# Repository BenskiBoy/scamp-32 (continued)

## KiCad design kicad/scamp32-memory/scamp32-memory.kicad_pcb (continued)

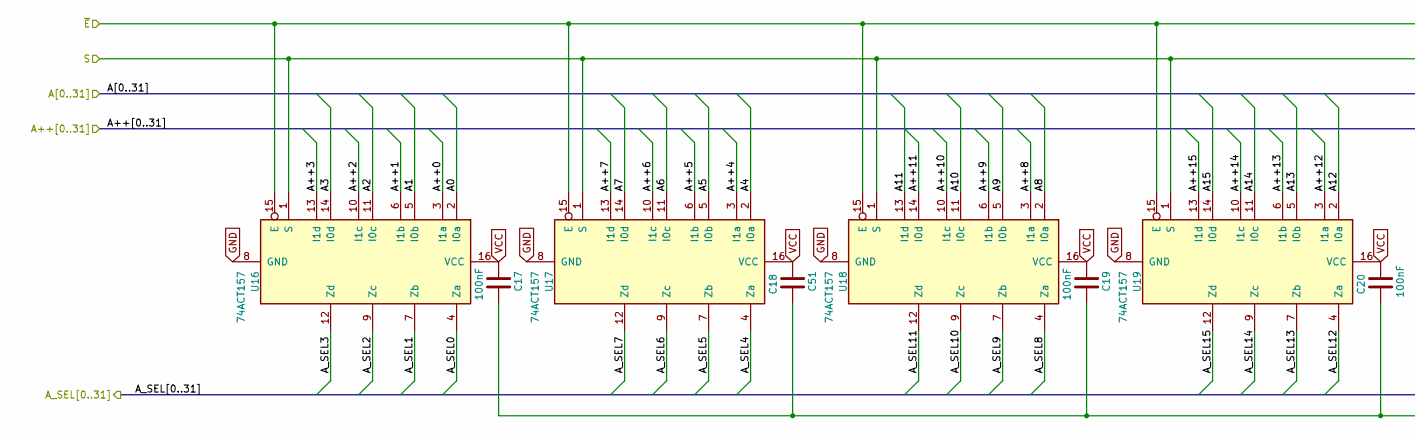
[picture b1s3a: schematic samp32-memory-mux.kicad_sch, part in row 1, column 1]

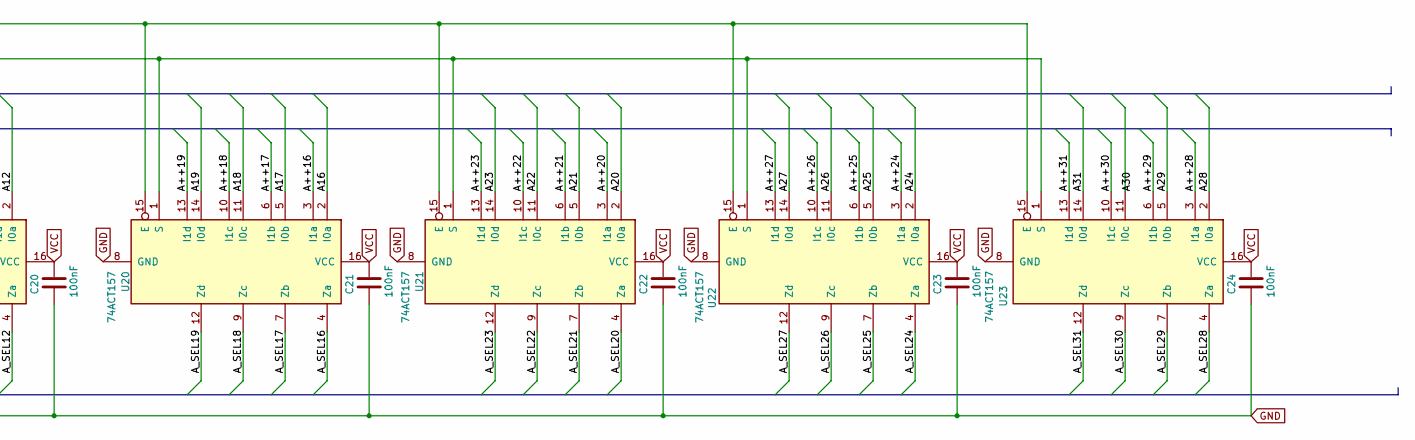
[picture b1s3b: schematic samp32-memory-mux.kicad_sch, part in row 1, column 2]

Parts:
C17, C19, C20, C21, C22, C23, C24: 100nF; C_0603_1608Metric
C18: C51; C_0603_1608Metric
U16, U17, U18, U19, U20, U21, U22, U23: 74ACT157; TSSOP-16_4.4x5mm_P0.65mm

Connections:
/A0: U16.2 (I0a); also elsewhere on the board
/A1: U16.5 (I0b); also elsewhere on the board
/A2: U16.11 (I0c); also elsewhere on the board
/A3: U16.14 (I0d); also elsewhere on the board
/A4: U17.2 (I0a); also elsewhere on the board
/A5: U17.5 (I0b); also elsewhere on the board
/A6: U17.11 (I0c); also elsewhere on the board
/A7: U17.14 (I0d); also elsewhere on the board
/A8: U18.2 (I0a); also elsewhere on the board
/A9: U18.5 (I0b); also elsewhere on the board
/A10: U18.11 (I0c); also elsewhere on the board
/A11: U18.13 (I1d); also elsewhere on the board
/A12: U19.2 (I0a); also elsewhere on the board
/A13: U19.5 (I0b); also elsewhere on the board
/A14: U19.11 (I0c); also elsewhere on the board
/A15: U19.14 (I0d); also elsewhere on the board
/A16: U20.2 (I0a); also elsewhere on the board
/A17: U20.5 (I0b); also elsewhere on the board
/A18: U20.11 (I0c); also elsewhere on the board
/A19: U20.14 (I0d); also elsewhere on the board
/A20: U21.2 (I0a); also elsewhere on the board
/A21: U21.5 (I0b); also elsewhere on the board
/A22: U21.11 (I0c); also elsewhere on the board
/A23: U21.14 (I0d); also elsewhere on the board
/A24: U22.2 (I0a); also elsewhere on the board
/A25: U22.5 (I0b); also elsewhere on the board
/A26: U22.11 (I0c); also elsewhere on the board
/A27: U22.14 (I0d); also elsewhere on the board
/A28: U23.2 (I0a); also elsewhere on the board
/A29: U23.5 (I0b); also elsewhere on the board
/A31: U23.14 (I0d); also elsewhere on the board
/samp32-memory-mux/A++0: U16.3 (I1a); also elsewhere on the board
/samp32-memory-mux/A++1: U16.6 (I1b); also elsewhere on the board
/samp32-memory-mux/A++2: U16.10 (I1c); also elsewhere on the board
/samp32-memory-mux/A++3: U16.13 (I1d); also elsewhere on the board
/samp32-memory-mux/A++4: U17.3 (I1a); also elsewhere on the board
/samp32-memory-mux/A++5: U17.6 (I1b); also elsewhere on the board
/samp32-memory-mux/A++6: U17.10 (I1c); also elsewhere on the board
/samp32-memory-mux/A++7: U17.13 (I1d); also elsewhere on the board
/samp32-memory-mux/A++8: U18.3 (I1a); also elsewhere on the board
/samp32-memory-mux/A++9: U18.6 (I1b); also elsewhere on the board
/samp32-memory-mux/A++10: U18.10 (I1c); also elsewhere on the board
/samp32-memory-mux/A++11: U18.14 (I0d); also elsewhere on the board
/samp32-memory-mux/A++12: U19.3 (I1a); also elsewhere on the board
/samp32-memory-mux/A++13: U19.6 (I1b); also elsewhere on the board
/samp32-memory-mux/A++14: U19.10 (I1c); also elsewhere on the board
/samp32-memory-mux/A++15: U19.13 (I1d); also elsewhere on the board
/samp32-memory-mux/A++16: U20.3 (I1a); also elsewhere on the board
/samp32-memory-mux/A++17: U20.6 (I1b); also elsewhere on the board
/samp32-memory-mux/A++18: U20.10 (I1c); also elsewhere on the board
/samp32-memory-mux/A++19: U20.13 (I1d); also elsewhere on the board
/samp32-memory-mux/A++20: U21.3 (I1a); also elsewhere on the board
/samp32-memory-mux/A++21: U21.6 (I1b); also elsewhere on the board
/samp32-memory-mux/A++22: U21.10 (I1c); also elsewhere on the board
/samp32-memory-mux/A++23: U21.13 (I1d); also elsewhere on the board
/samp32-memory-mux/A++24: U22.3 (I1a); also elsewhere on the board
/samp32-memory-mux/A++25: U22.6 (I1b); also elsewhere on the board
/samp32-memory-mux/A++26: U22.10 (I1c); also elsewhere on the board
/samp32-memory-mux/A++27: U22.13 (I1d); also elsewhere on the board
/samp32-memory-mux/A++28: U23.3 (I1a); also elsewhere on the board
/samp32-memory-mux/A++29: U23.6 (I1b); also elsewhere on the board
/samp32-memory-mux/A++30: U23.10 (I1c); also elsewhere on the board
/samp32-memory-mux/A++31: U23.13 (I1d); also elsewhere on the board
/samp32-memory-mux/A_SEL0: U16.4 (Za); also elsewhere on the board
/samp32-memory-mux/A_SEL1: U16.7 (Zb); also elsewhere on the board
/samp32-memory-mux/A_SEL2: U16.9 (Zc); also elsewhere on the board
/samp32-memory-mux/A_SEL3: U16.12 (Zd); also elsewhere on the board
/samp32-memory-mux/A_SEL4: U17.4 (Za); also elsewhere on the board
/samp32-memory-mux/A_SEL5: U17.7 (Zb); also elsewhere on the board
/samp32-memory-mux/A_SEL6: U17.9 (Zc); also elsewhere on the board
/samp32-memory-mux/A_SEL7: U17.12 (Zd); also elsewhere on the board
/samp32-memory-mux/A_SEL8: U18.4 (Za); also elsewhere on the board
/samp32-memory-mux/A_SEL9: U18.7 (Zb); also elsewhere on the board
/samp32-memory-mux/A_SEL10: U18.9 (Zc); also elsewhere on the board
/samp32-memory-mux/A_SEL11: U18.12 (Zd); also elsewhere on the board
/samp32-memory-mux/A_SEL12: U19.4 (Za); also elsewhere on the board
/samp32-memory-mux/A_SEL13: U19.7 (Zb); also elsewhere on the board
/samp32-memory-mux/A_SEL14: U19.9 (Zc); also elsewhere on the board
/samp32-memory-mux/A_SEL15: U19.12 (Zd); also elsewhere on the board
/samp32-memory-mux/A_SEL16: U20.4 (Za); also elsewhere on the board
/samp32-memory-mux/A_SEL17: U20.7 (Zb); also elsewhere on the board
/samp32-memory-mux/A_SEL18: U20.9 (Zc); also elsewhere on the board
/samp32-memory-mux/A_SEL19: U20.12 (Zd)
/samp32-memory-mux/A_SEL20: U21.4 (Za)
/samp32-memory-mux/A_SEL21: U21.7 (Zb)
/samp32-memory-mux/A_SEL22: U21.9 (Zc)
/samp32-memory-mux/A_SEL23: U21.12 (Zd)
/samp32-memory-mux/A_SEL24: U22.4 (Za)
/samp32-memory-mux/A_SEL25: U22.7 (Zb)
/samp32-memory-mux/A_SEL26: U22.9 (Zc)
/samp32-memory-mux/A_SEL27: U22.12 (Zd)
/samp32-memory-mux/A_SEL28: U23.4 (Za)
/samp32-memory-mux/A_SEL29: U23.7 (Zb)
/samp32-memory-mux/A_SEL30: U23.9 (Zc)
/samp32-memory-mux/A_SEL31: U23.12 (Zd)
/samp32-memory-mux/S: U16.1 (S), U17.1 (S), U18.1 (S), U19.1 (S), U20.1 (S), U21.1 (S), U22.1 (S), U23.1 (S); also elsewhere on the board
GND: C17.2, C18.1, C19.2, C20.1, C21.1, C22.1, C23.1, C24.1, U16.8 (GND), U16.15 (E), U17.8 (GND), U17.15 (E), U18.8 (GND), U18.15 (E), U19.8 (GND), U19.15 (E), U20.8 (GND), U20.15 (E), U21.8 (GND), U21.15 (E), U22.8 (GND), U22.15 (E), U23.8 (GND), U23.15 (E); also elsewhere on the board
VCC: C17.1, C18.2, C19.1, C20.2, C21.2, C22.2, C23.2, C24.2, U16.16 (VCC), U17.16 (VCC), U18.16 (VCC), U19.16 (VCC), U20.16 (VCC), U21.16 (VCC), U22.16 (VCC), U23.16 (VCC); also elsewhere on the board

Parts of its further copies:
C25, C27, C28, C29, C30, C31, C32: 100nF; C_0603_1608Metric
C26: C51; C_0603_1608Metric
U24, U25, U26, U27, U28, U29, U30, U31: 74ACT157; TSSOP-16_4.4x5mm_P0.65mm

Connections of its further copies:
/A0: U24.2 (I0a); also elsewhere on the board
/A1: U24.5 (I0b); also elsewhere on the board
/A2: U24.11 (I0c); also elsewhere on the board
/A3: U24.14 (I0d); also elsewhere on the board
/A4: U25.2 (I0a); also elsewhere on the board
/A5: U25.5 (I0b); also elsewhere on the board
/A6: U25.11 (I0c); also elsewhere on the board
/A7: U25.14 (I0d); also elsewhere on the board
/A8: U26.2 (I0a); also elsewhere on the board
/A9: U26.5 (I0b); also elsewhere on the board
/A10: U26.11 (I0c); also elsewhere on the board
/A11: U26.13 (I1d); also elsewhere on the board
/A12: U27.2 (I0a); also elsewhere on the board
/A13: U27.5 (I0b); also elsewhere on the board
/A14: U27.11 (I0c); also elsewhere on the board
/A15: U27.14 (I0d); also elsewhere on the board
/A16: U28.2 (I0a); also elsewhere on the board
/A17: U28.5 (I0b); also elsewhere on the board
/A18: U28.11 (I0c); also elsewhere on the board
/A19: U28.14 (I0d); also elsewhere on the board
/A20: U29.2 (I0a); also elsewhere on the board
/A21: U29.5 (I0b); also elsewhere on the board
/A22: U29.11 (I0c); also elsewhere on the board
/A23: U29.14 (I0d); also elsewhere on the board
/A24: U30.2 (I0a); also elsewhere on the board
/A25: U30.5 (I0b); also elsewhere on the board
/A26: U30.11 (I0c); also elsewhere on the board
/A27: U30.14 (I0d); also elsewhere on the board
/A28: U31.2 (I0a); also elsewhere on the board
/A29: U31.5 (I0b); also elsewhere on the board
/A31: U31.14 (I0d); also elsewhere on the board
/samp32-memory-mux1/A_SEL19: U28.12 (Zd)
/samp32-memory-mux1/A_SEL20: U29.4 (Za)
/samp32-memory-mux1/A_SEL21: U29.7 (Zb)
/samp32-memory-mux1/A_SEL22: U29.9 (Zc)
/samp32-memory-mux1/A_SEL23: U29.12 (Zd)
/samp32-memory-mux1/A_SEL24: U30.4 (Za)
/samp32-memory-mux1/A_SEL25: U30.7 (Zb)
/samp32-memory-mux1/A_SEL26: U30.9 (Zc)
/samp32-memory-mux1/A_SEL27: U30.12 (Zd)
/samp32-memory-mux1/A_SEL28: U31.4 (Za)
/samp32-memory-mux1/A_SEL29: U31.7 (Zb)
/samp32-memory-mux1/A_SEL30: U31.9 (Zc)
/samp32-memory-mux1/A_SEL31: U31.12 (Zd)
/samp32-memory-mux1/S: U24.1 (S), U25.1 (S), U26.1 (S), U27.1 (S), U28.1 (S), U29.1 (S), U30.1 (S), U31.1 (S); also elsewhere on the board
/samp32-memory-mux/A++0: U24.3 (I1a); also elsewhere on the board
/samp32-memory-mux/A++1: U24.6 (I1b); also elsewhere on the board
/samp32-memory-mux/A++2: U24.10 (I1c); also elsewhere on the board
/samp32-memory-mux/A++3: U24.13 (I1d); also elsewhere on the board
/samp32-memory-mux/A++4: U25.3 (I1a); also elsewhere on the board
/samp32-memory-mux/A++5: U25.6 (I1b); also elsewhere on the board
/samp32-memory-mux/A++6: U25.10 (I1c); also elsewhere on the board
/samp32-memory-mux/A++7: U25.13 (I1d); also elsewhere on the board
/samp32-memory-mux/A++8: U26.3 (I1a); also elsewhere on the board
/samp32-memory-mux/A++9: U26.6 (I1b); also elsewhere on the board
/samp32-memory-mux/A++10: U26.10 (I1c); also elsewhere on the board
/samp32-memory-mux/A++11: U26.14 (I0d); also elsewhere on the board
/samp32-memory-mux/A++12: U27.3 (I1a); also elsewhere on the board
/samp32-memory-mux/A++13: U27.6 (I1b); also elsewhere on the board
/samp32-memory-mux/A++14: U27.10 (I1c); also elsewhere on the board
/samp32-memory-mux/A++15: U27.13 (I1d); also elsewhere on the board
/samp32-memory-mux/A++16: U28.3 (I1a); also elsewhere on the board
/samp32-memory-mux/A++17: U28.6 (I1b); also elsewhere on the board
/samp32-memory-mux/A++18: U28.10 (I1c); also elsewhere on the board
/samp32-memory-mux/A++19: U28.13 (I1d); also elsewhere on the board
/samp32-memory-mux/A++20: U29.3 (I1a); also elsewhere on the board
/samp32-memory-mux/A++21: U29.6 (I1b); also elsewhere on the board
/samp32-memory-mux/A++22: U29.10 (I1c); also elsewhere on the board
/samp32-memory-mux/A++23: U29.13 (I1d); also elsewhere on the board
/samp32-memory-mux/A++24: U30.3 (I1a); also elsewhere on the board
/samp32-memory-mux/A++25: U30.6 (I1b); also elsewhere on the board
/samp32-memory-mux/A++26: U30.10 (I1c); also elsewhere on the board
/samp32-memory-mux/A++27: U30.13 (I1d); also elsewhere on the board
/samp32-memory-mux/A++28: U31.3 (I1a); also elsewhere on the board
/samp32-memory-mux/A++29: U31.6 (I1b); also elsewhere on the board
/samp32-memory-mux/A++30: U31.10 (I1c); also elsewhere on the board
/samp32-memory-mux/A++31: U31.13 (I1d); also elsewhere on the board
/samp32-memory-mux/A_SEL0: U24.4 (Za); also elsewhere on the board
/samp32-memory-mux/A_SEL1: U24.7 (Zb); also elsewhere on the board
/samp32-memory-mux/A_SEL2: U24.9 (Zc); also elsewhere on the board
/samp32-memory-mux/A_SEL3: U24.12 (Zd); also elsewhere on the board
/samp32-memory-mux/A_SEL4: U25.4 (Za); also elsewhere on the board
/samp32-memory-mux/A_SEL5: U25.7 (Zb); also elsewhere on the board
/samp32-memory-mux/A_SEL6: U25.9 (Zc); also elsewhere on the board
/samp32-memory-mux/A_SEL7: U25.12 (Zd); also elsewhere on the board
/samp32-memory-mux/A_SEL8: U26.4 (Za); also elsewhere on the board
/samp32-memory-mux/A_SEL9: U26.7 (Zb); also elsewhere on the board
/samp32-memory-mux/A_SEL10: U26.9 (Zc); also elsewhere on the board
/samp32-memory-mux/A_SEL11: U26.12 (Zd); also elsewhere on the board
/samp32-memory-mux/A_SEL12: U27.4 (Za); also elsewhere on the board
/samp32-memory-mux/A_SEL13: U27.7 (Zb); also elsewhere on the board
/samp32-memory-mux/A_SEL14: U27.9 (Zc); also elsewhere on the board
/samp32-memory-mux/A_SEL15: U27.12 (Zd); also elsewhere on the board
/samp32-memory-mux/A_SEL16: U28.4 (Za); also elsewhere on the board
/samp32-memory-mux/A_SEL17: U28.7 (Zb); also elsewhere on the board
/samp32-memory-mux/A_SEL18: U28.9 (Zc); also elsewhere on the board
GND: C25.2, C26.1, C27.2, C28.1, C29.1, C30.1, C31.1, C32.1, U24.8 (GND), U24.15 (E), U25.8 (GND), U25.15 (E), U26.8 (GND), U26.15 (E), U27.8 (GND), U27.15 (E), U28.8 (GND), U28.15 (E), U29.8 (GND), U29.15 (E), U30.8 (GND), U30.15 (E), U31.8 (GND), U31.15 (E); also elsewhere on the board
VCC: C25.1, C26.2, C27.1, C28.2, C29.2, C30.2, C31.2, C32.2, U24.16 (VCC), U25.16 (VCC), U26.16 (VCC), U27.16 (VCC), U28.16 (VCC), U29.16 (VCC), U30.16 (VCC), U31.16 (VCC); also elsewhere on the board

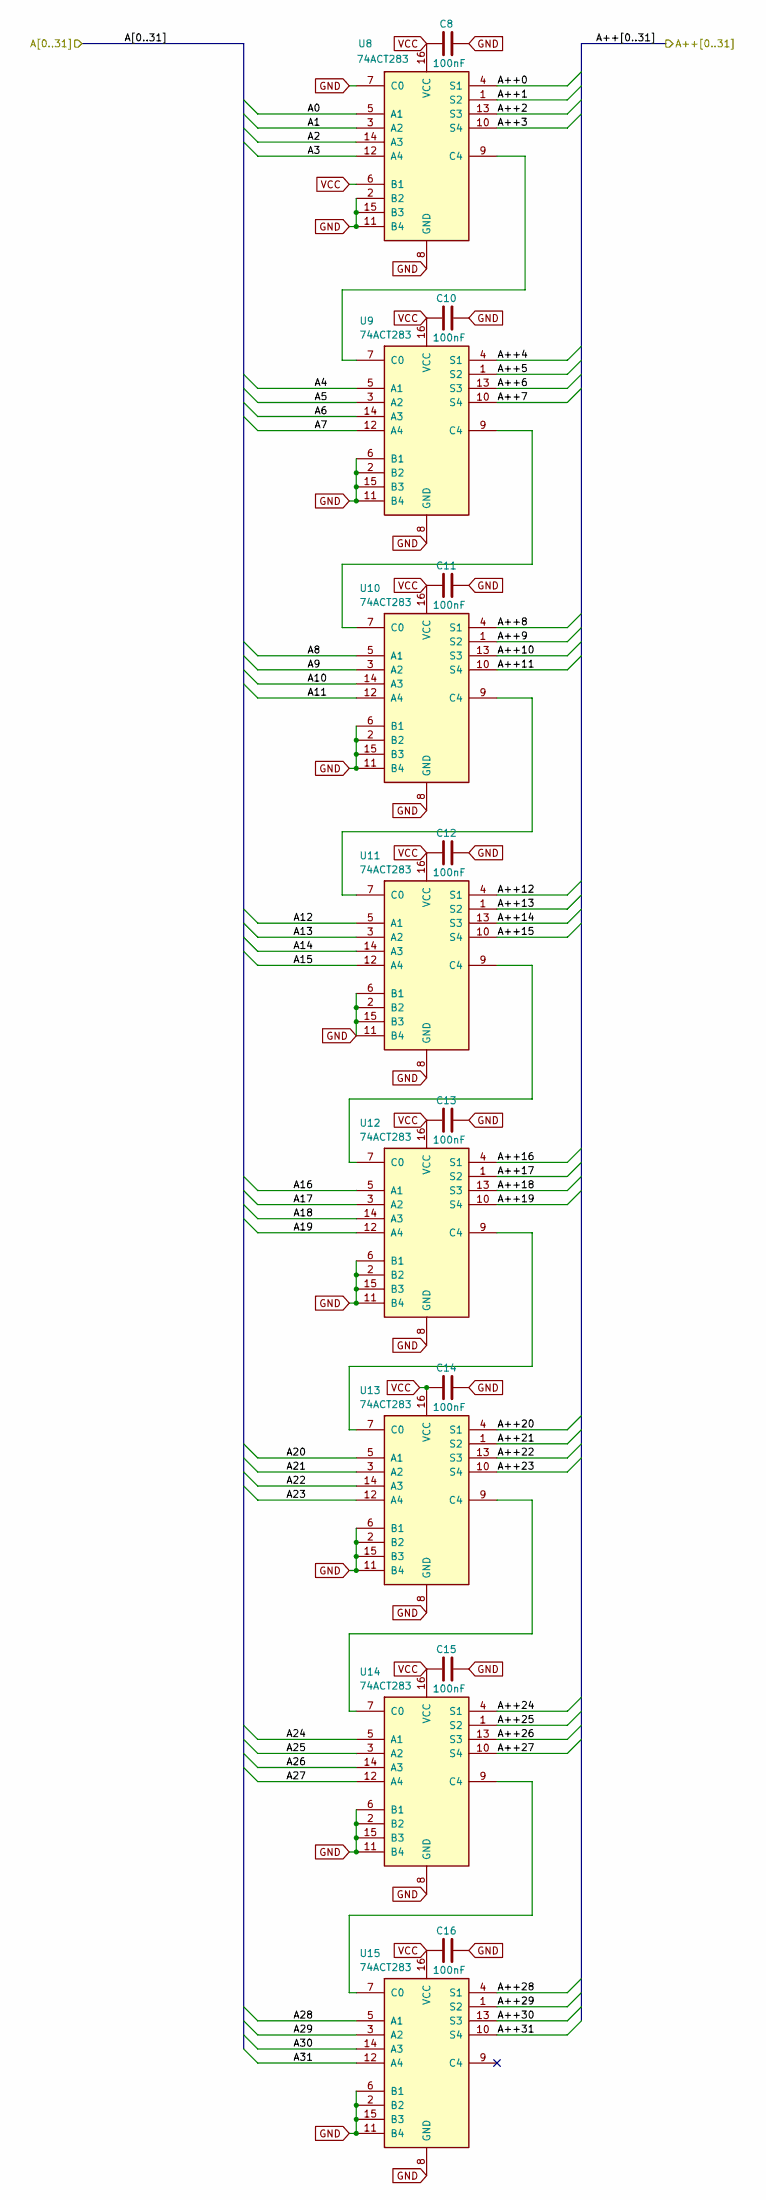
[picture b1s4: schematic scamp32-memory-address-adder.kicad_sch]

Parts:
C8, C10, C11, C12, C13, C14, C15, C16: 100nF; C_0603_1608Metric
U8, U9, U10, U11, U12, U13, U14, U15: 74ACT283; TSSOP-16_4.4x5mm_P0.65mm

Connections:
/A0: U8.5 (A1); also elsewhere on the board
/A1: U8.3 (A2); also elsewhere on the board
/A2: U8.14 (A3); also elsewhere on the board
/A3: U8.12 (A4); also elsewhere on the board
/A4: U9.5 (A1); also elsewhere on the board
/A5: U9.3 (A2); also elsewhere on the board
/A6: U9.14 (A3); also elsewhere on the board
/A7: U9.12 (A4); also elsewhere on the board
/A8: U10.5 (A1); also elsewhere on the board
/A9: U10.3 (A2); also elsewhere on the board
/A10: U10.14 (A3); also elsewhere on the board
/A11: U10.12 (A4); also elsewhere on the board
/A12: U11.5 (A1); also elsewhere on the board
/A13: U11.3 (A2); also elsewhere on the board
/A14: U11.14 (A3); also elsewhere on the board
/A15: U11.12 (A4); also elsewhere on the board
/A16: U12.5 (A1); also elsewhere on the board
/A17: U12.3 (A2); also elsewhere on the board
/A18: U12.14 (A3); also elsewhere on the board
/A19: U12.12 (A4); also elsewhere on the board
/A20: U13.5 (A1); also elsewhere on the board
/A21: U13.3 (A2); also elsewhere on the board
/A22: U13.14 (A3); also elsewhere on the board
/A23: U13.12 (A4); also elsewhere on the board
/A24: U14.5 (A1); also elsewhere on the board
/A25: U14.3 (A2); also elsewhere on the board
/A26: U14.14 (A3); also elsewhere on the board
/A27: U14.12 (A4); also elsewhere on the board
/A28: U15.5 (A1); also elsewhere on the board
/A29: U15.3 (A2); also elsewhere on the board
/A30: U15.14 (A3); also elsewhere on the board
/A31: U15.12 (A4); also elsewhere on the board
/samp32-memory-mux/A++0: U8.4 (S1); also elsewhere on the board
/samp32-memory-mux/A++1: U8.1 (S2); also elsewhere on the board
/samp32-memory-mux/A++2: U8.13 (S3); also elsewhere on the board
/samp32-memory-mux/A++3: U8.10 (S4); also elsewhere on the board
/samp32-memory-mux/A++4: U9.4 (S1); also elsewhere on the board
/samp32-memory-mux/A++5: U9.1 (S2); also elsewhere on the board
/samp32-memory-mux/A++6: U9.13 (S3); also elsewhere on the board
/samp32-memory-mux/A++7: U9.10 (S4); also elsewhere on the board
/samp32-memory-mux/A++8: U10.4 (S1); also elsewhere on the board
/samp32-memory-mux/A++9: U10.1 (S2); also elsewhere on the board
/samp32-memory-mux/A++10: U10.13 (S3); also elsewhere on the board
/samp32-memory-mux/A++11: U10.10 (S4); also elsewhere on the board
/samp32-memory-mux/A++12: U11.4 (S1); also elsewhere on the board
/samp32-memory-mux/A++13: U11.1 (S2); also elsewhere on the board
/samp32-memory-mux/A++14: U11.13 (S3); also elsewhere on the board
/samp32-memory-mux/A++15: U11.10 (S4); also elsewhere on the board
/samp32-memory-mux/A++16: U12.4 (S1); also elsewhere on the board
/samp32-memory-mux/A++17: U12.1 (S2); also elsewhere on the board
/samp32-memory-mux/A++18: U12.13 (S3); also elsewhere on the board
/samp32-memory-mux/A++19: U12.10 (S4); also elsewhere on the board
/samp32-memory-mux/A++20: U13.4 (S1); also elsewhere on the board
/samp32-memory-mux/A++21: U13.1 (S2); also elsewhere on the board
/samp32-memory-mux/A++22: U13.13 (S3); also elsewhere on the board
/samp32-memory-mux/A++23: U13.10 (S4); also elsewhere on the board
/samp32-memory-mux/A++24: U14.4 (S1); also elsewhere on the board
/samp32-memory-mux/A++25: U14.1 (S2); also elsewhere on the board
/samp32-memory-mux/A++26: U14.13 (S3); also elsewhere on the board
/samp32-memory-mux/A++27: U14.10 (S4); also elsewhere on the board
/samp32-memory-mux/A++28: U15.4 (S1); also elsewhere on the board
/samp32-memory-mux/A++29: U15.1 (S2); also elsewhere on the board
/samp32-memory-mux/A++30: U15.13 (S3); also elsewhere on the board
/samp32-memory-mux/A++31: U15.10 (S4); also elsewhere on the board
GND: C8.2, C10.2, C11.2, C12.2, C13.2, C14.2, C15.2, C16.2, U8.2 (B2), U8.7 (C0), U8.8 (GND), U8.11 (B4), U8.15 (B3), U9.2 (B2), U9.6 (B1), U9.8 (GND), U9.11 (B4), U9.15 (B3), U10.2 (B2), U10.6 (B1), U10.8 (GND), U10.11 (B4), U10.15 (B3), U11.2 (B2), U11.6 (B1), U11.8 (GND), U11.11 (B4), U11.15 (B3), U12.2 (B2), U12.6 (B1), U12.8 (GND), U12.11 (B4), U12.15 (B3), U13.2 (B2), U13.6 (B1), U13.8 (GND), U13.11 (B4), U13.15 (B3), U14.2 (B2), U14.6 (B1), U14.8 (GND), U14.11 (B4), U14.15 (B3), U15.2 (B2), U15.6 (B1), U15.8 (GND), U15.11 (B4), U15.15 (B3); also elsewhere on the board
unnamed: U8.9 (C4), U9.7 (C0)
unnamed: U9.9 (C4), U10.7 (C0)
unnamed: U10.9 (C4), U11.7 (C0)
unnamed: U11.9 (C4), U12.7 (C0)
unnamed: U12.9 (C4), U13.7 (C0)
unnamed: U13.9 (C4), U14.7 (C0)
unnamed: U14.9 (C4), U15.7 (C0)
VCC: C8.1, C10.1, C11.1, C12.1, C13.1, C14.1, C15.1, C16.1, U8.6 (B1), U8.16 (VCC), U9.16 (VCC), U10.16 (VCC), U11.16 (VCC), U12.16 (VCC), U13.16 (VCC), U14.16 (VCC), U15.16 (VCC); also elsewhere on the board

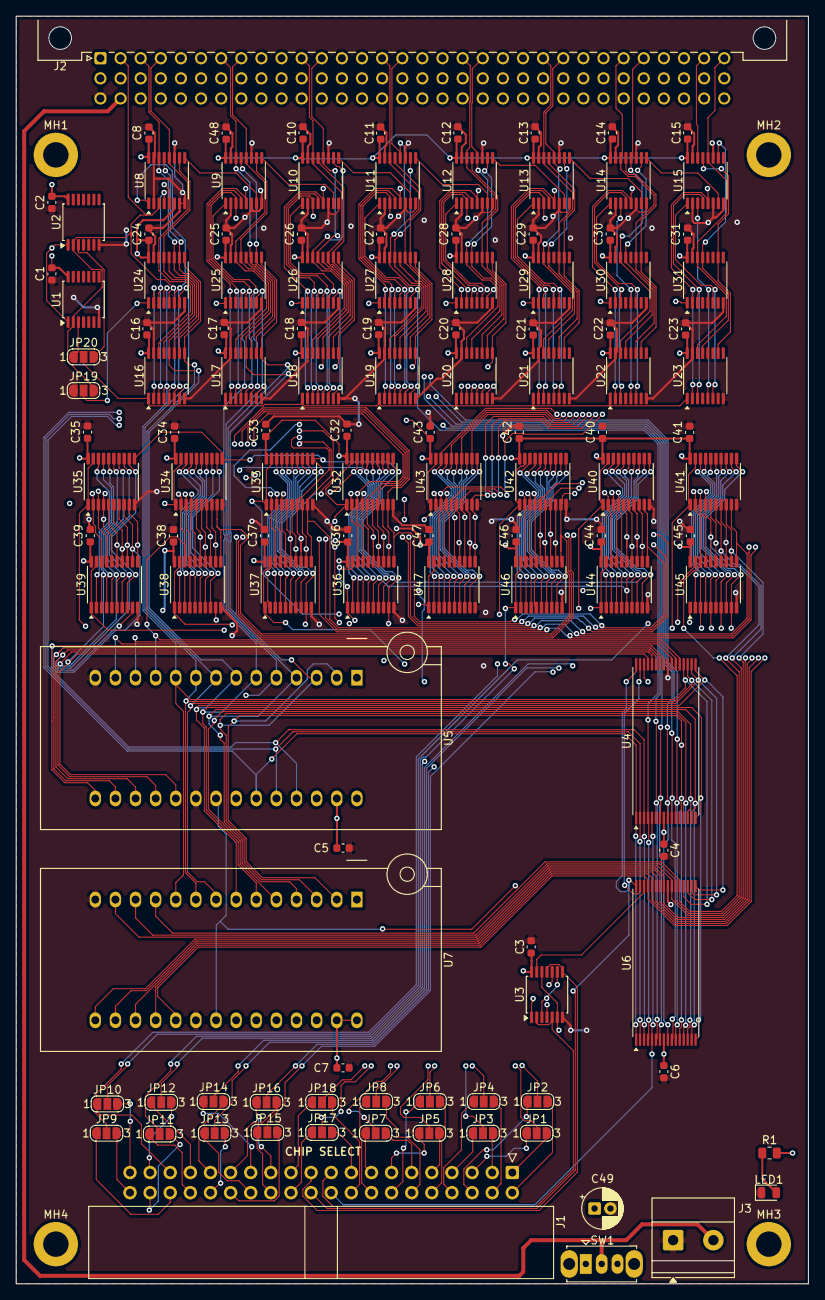
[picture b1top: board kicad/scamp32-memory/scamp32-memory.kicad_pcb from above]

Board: 4 copper layers, 100.0 x 160.0 mm, 125 parts (0 on the bottom side), 208 nets.

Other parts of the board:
MH1, MH2, MH3, MH4: MountingHole_3.2mm_M3_DIN965_Pad
